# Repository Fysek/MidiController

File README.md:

# MidiController

The goal of the project is to create and test an extension board with two SIPO 74HC595 shift registers.
The system will work with Arduino Uno.

The registers function is to expand the number of input and output ports of the Arduino board. The whole will work as a controller for the MIDI keyboard.

The use of shift registers allows you to use every available keyboard.

There are two version of the board: 1. Board with additional connections and LED diodes to observe input and outputs
                                    2. Board without connections and LEDs

Tests has been manually executed in NI TestStand. The board was connected via NI myRIO.

## Board without testpoints:

## Board with testpoints:

## Testing with NI myRIO:

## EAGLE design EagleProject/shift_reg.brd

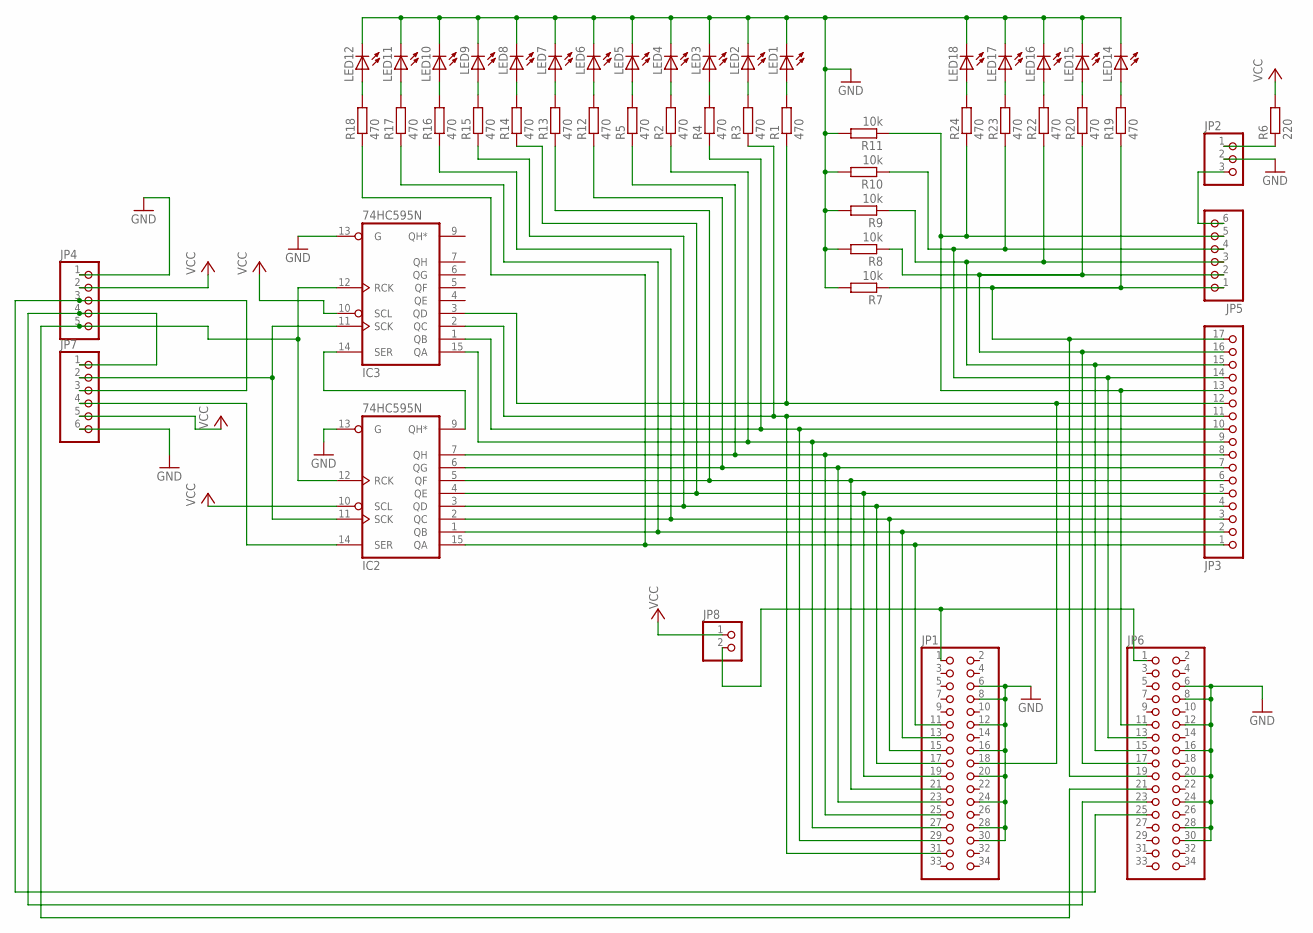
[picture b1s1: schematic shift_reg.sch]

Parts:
IC2, IC3: 74HC595N; DIL16
JP1, JP6: PINHD-2X17; 2X17
JP2: PINHD-1X3; 1X03
JP3: PINHD-1X17; 1X17
JP4: PINHD-1X5; 1X05
JP5, JP7: PINHD-1X6; 1X06
JP8: PINHD-1X2; 1X02
LED1, LED2, LED3, LED4, LED5, LED6, LED7, LED8, LED9, LED10, LED11, LED12, LED14, LED15, LED16, LED17, LED18: LED3MM
R1, R2, R3, R4, R5, R12, R13, R14, R15, R16, R17, R18, R19, R20, R22, R23, R24: 470; 0207/10
R6: 220; 0207/10
R7, R8, R9, R10, R11: 10k; 0207/10

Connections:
GND: IC2.8 (GND), IC2.13 (G), IC3.8 (GND), IC3.13 (G), JP1.6, JP1.8, JP1.12, JP1.16, JP1.20, JP1.24, JP1.28, JP1.30, JP2.2, JP4.1, JP6.6, JP6.8, JP6.12, JP6.16, JP6.20, JP6.24, JP6.28, JP6.30, JP7.6, LED1.K (C), LED2.K (C), LED3.K (C), LED4.K (C), LED5.K (C), LED6.K (C), LED7.K (C), LED8.K (C), LED9.K (C), LED10.K (C), LED11.K (C), LED12.K (C), LED14.K (C), LED15.K (C), LED16.K (C), LED17.K (C), LED18.K (C), R7.2, R8.2, R9.2, R10.2, R11.2
unnamed: JP3.13, JP5.5, JP6.11, R11.1, R24.1
unnamed: JP2.3, JP5.6
unnamed: JP3.15, JP5.3, JP6.15, R9.1, R22.1
unnamed: LED1.A, R1.2
unnamed: JP1.1, JP6.1, JP8.2
unnamed: IC2.12 (RCK), IC3.12 (RCK), JP4.5, JP6.21
unnamed: IC2.7 (QH), JP1.25, JP3.8, R5.1
unnamed: IC3.15 (QA), JP1.27, JP3.9, R2.1
unnamed: IC2.9 (QH*), IC3.14 (SER)
unnamed: IC2.14 (SER), JP7.4
unnamed: JP3.16, JP5.2, JP6.17, R8.1, R20.1
unnamed: JP2.1, R6.1
unnamed: IC2.5 (QF), JP1.21, JP3.6, R13.1
unnamed: JP3.17, JP5.1, JP6.19, R7.1, R19.1
unnamed: LED2.A, R3.2
unnamed: LED3.A, R4.2
unnamed: JP3.14, JP5.4, JP6.13, R10.1, R23.1
unnamed: LED4.A, R2.2
unnamed: LED5.A, R5.2
unnamed: LED9.A, R15.2
unnamed: LED8.A, R14.2
unnamed: IC3.1 (QB), JP1.29, JP3.10, R4.1
unnamed: IC3.2 (QC), JP1.31, JP3.11, R3.1
unnamed: IC3.3 (QD), JP1.18, JP3.12, R1.1
unnamed: LED7.A, R13.2
unnamed: LED6.A, R12.2
unnamed: LED10.A, R16.2
unnamed: LED11.A, R17.2
unnamed: LED12.A, R18.2
unnamed: JP4.3, JP6.25, JP7.3
unnamed: JP4.4, JP6.23, JP7.1
unnamed: IC2.11 (SCK), IC3.11 (SCK), JP7.2
unnamed: IC2.1 (QB), JP1.13, JP3.2, R17.1
unnamed: IC2.6 (QG), JP1.23, JP3.7, R12.1
unnamed: IC2.15 (QA), JP1.11, JP3.1, R18.1
unnamed: LED14.A, R19.2
unnamed: LED15.A, R20.2
unnamed: LED16.A, R22.2
unnamed: LED17.A, R23.2
unnamed: LED18.A, R24.2
unnamed: IC2.2 (QC), JP1.15, JP3.3, R16.1
unnamed: IC2.4 (QE), JP1.19, JP3.5, R14.1
unnamed: IC2.3 (QD), JP1.17, JP3.4, R15.1
VCC: IC2.10 (SCL), IC2.16 (VCC), IC3.10 (SCL), IC3.16 (VCC), JP4.2, JP7.5, JP8.1, R6.2

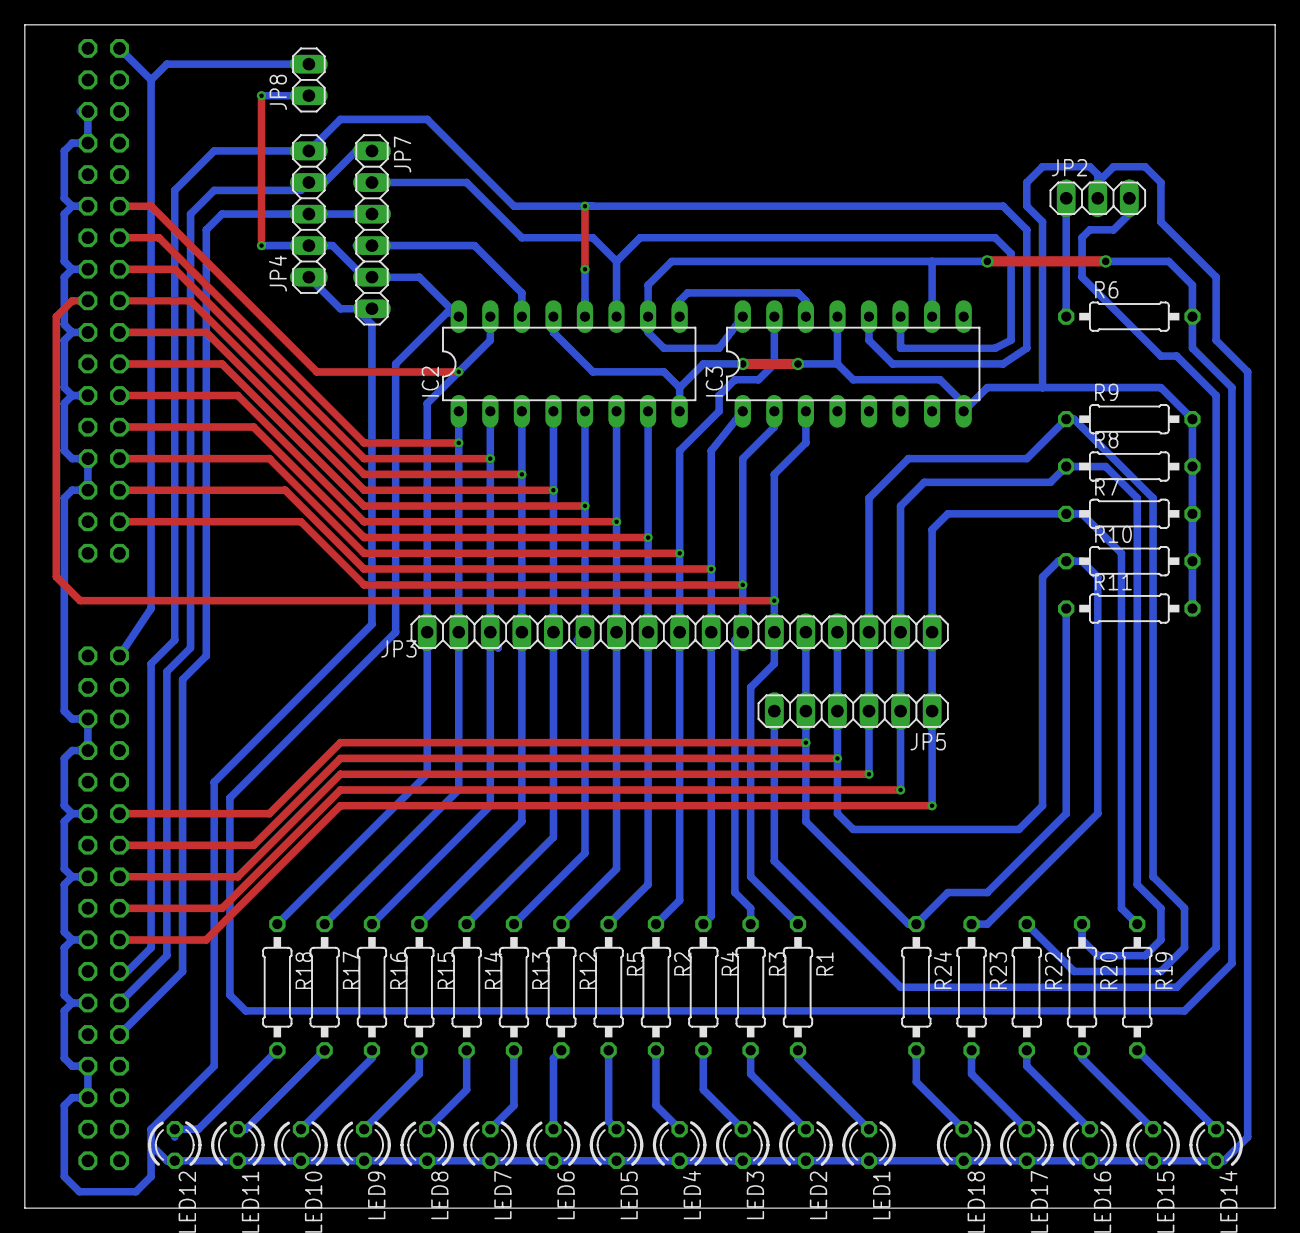
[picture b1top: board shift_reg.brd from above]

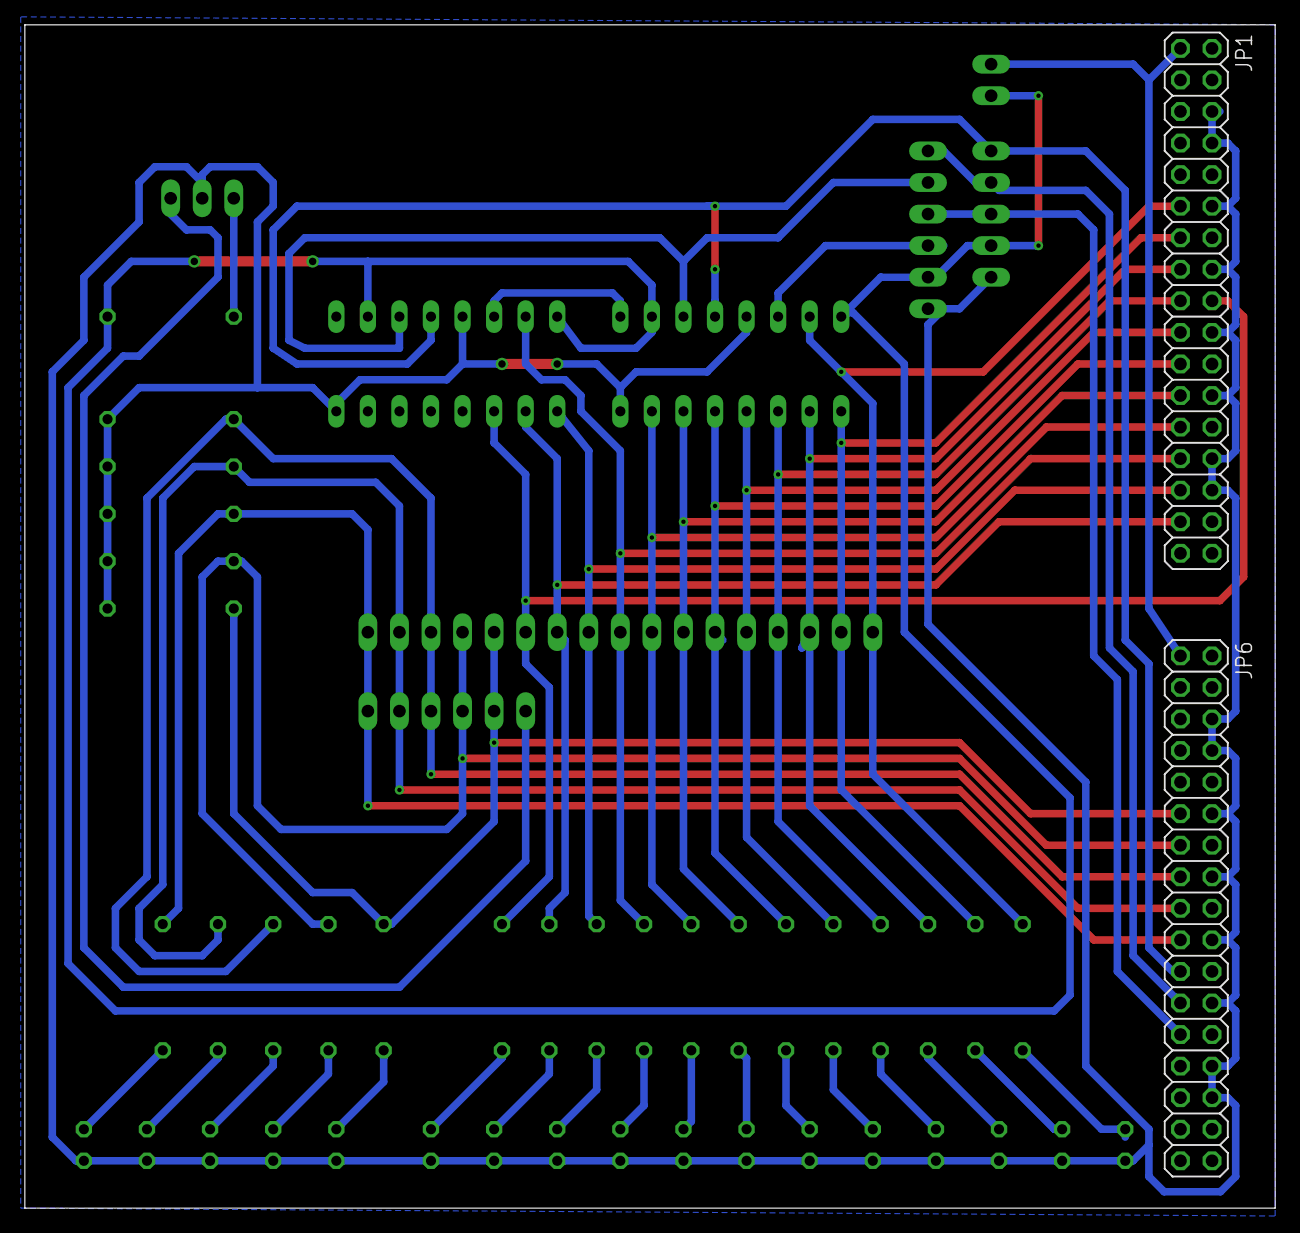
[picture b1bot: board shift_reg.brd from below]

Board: 2 copper layers, 100.6 x 95.2 mm, 50 parts (2 on the bottom side), 45 nets.

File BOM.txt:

Part  Value    Device       Package Description                        
IC2   74HC595N 74HC595N     DIL16   8-bit SHIFT REGISTER, output latch 
IC3   74HC595N 74HC595N     DIL16   8-bit SHIFT REGISTER, output latch 
JP1            PINHD-2X17   2X17    PIN HEADER                         
JP2            PINHD-1X3    1X03    PIN HEADER                         
JP3            PINHD-1X17   1X17    PIN HEADER                         
JP4            PINHD-1X5    1X05    PIN HEADER                         
JP5            PINHD-1X6    1X06    PIN HEADER                         
JP6            PINHD-2X17   2X17    PIN HEADER                         
JP7            PINHD-1X6    1X06    PIN HEADER                         
JP8            PINHD-1X2    1X02    PIN HEADER                         
LED1           LED3MM       LED3MM  LED                                
LED2           LED3MM       LED3MM  LED                                
LED3           LED3MM       LED3MM  LED                                
LED4           LED3MM       LED3MM  LED                                
LED5           LED3MM       LED3MM  LED                                
LED6           LED3MM       LED3MM  LED                                
LED7           LED3MM       LED3MM  LED                                
LED8           LED3MM       LED3MM  LED                                
LED9           LED3MM       LED3MM  LED                                
LED10          LED3MM       LED3MM  LED                                
LED11          LED3MM       LED3MM  LED                                
LED12          LED3MM       LED3MM  LED                                
LED14          LED3MM       LED3MM  LED                                
LED15          LED3MM       LED3MM  LED                                
LED16          LED3MM       LED3MM  LED                                
LED17          LED3MM       LED3MM  LED                                
LED18          LED3MM       LED3MM  LED                                
R1    470      R-EU_0207/10 0207/10 RESISTOR, European symbol          
R2    470      R-EU_0207/10 0207/10 RESISTOR, European symbol          
R3    470      R-EU_0207/10 0207/10 RESISTOR, European symbol          
R4    470      R-EU_0207/10 0207/10 RESISTOR, European symbol          
R5    470      R-EU_0207/10 0207/10 RESISTOR, European symbol          
R6    220      R-EU_0207/10 0207/10 RESISTOR, European symbol          
R7    10k      R-EU_0207/10 0207/10 RESISTOR, European symbol          
R8    10k      R-EU_0207/10 0207/10 RESISTOR, European symbol          
R9    10k      R-EU_0207/10 0207/10 RESISTOR, European symbol          
R10   10k      R-EU_0207/10 0207/10 RESISTOR, European symbol          
R11   10k      R-EU_0207/10 0207/10 RESISTOR, European symbol          
R12   470      R-EU_0207/10 0207/10 RESISTOR, European symbol          
R13   470      R-EU_0207/10 0207/10 RESISTOR, European symbol          
R14   470      R-EU_0207/10 0207/10 RESISTOR, European symbol          
R15   470      R-EU_0207/10 0207/10 RESISTOR, European symbol          
R16   470      R-EU_0207/10 0207/10 RESISTOR, European symbol          
R17   470      R-EU_0207/10 0207/10 RESISTOR, European symbol          
R18   470      R-EU_0207/10 0207/10 RESISTOR, European symbol          
R19   470      R-EU_0207/10 0207/10 RESISTOR, European symbol          
R20   470      R-EU_0207/10 0207/10 RESISTOR, European symbol          
R22   470      R-EU_0207/10 0207/10 RESISTOR, European symbol          
R23   470      R-EU_0207/10 0207/10 RESISTOR, European symbol          
R24   470      R-EU_0207/10 0207/10 RESISTOR, European symbol

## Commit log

2019-11-15 small changes
2019-11-15 Arduino dir added
2021-11-28 Updated size of pics on readme
2021-11-28 resized pictures
2021-11-28 added pics with ni myrio to readme
